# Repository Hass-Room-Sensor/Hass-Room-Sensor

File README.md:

# HASS Room Sensor

Home Assistant compatible sensor platform with ZigBee and ESPHome functionality.

## Hardware

* PCB: [`ecad/README.md`](ecad/README.md)
* Housing: [`mcad/README.md`](mcad/README.md)

## Firmware

For this please take a look at [`firmware/README.md`](firmware/README.md).

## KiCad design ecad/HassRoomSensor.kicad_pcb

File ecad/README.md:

# ecad

Room Sensor for Home Assistant.
There are two sensors that can be populated.

## BME690

* Temperature
* Humidity
* Pressure
* air quality (IAQ) level

## SCD4x

* Temperature
* Humidity
* CO2

The SCD4x has a higher accuracy with the pressure value of the BME690

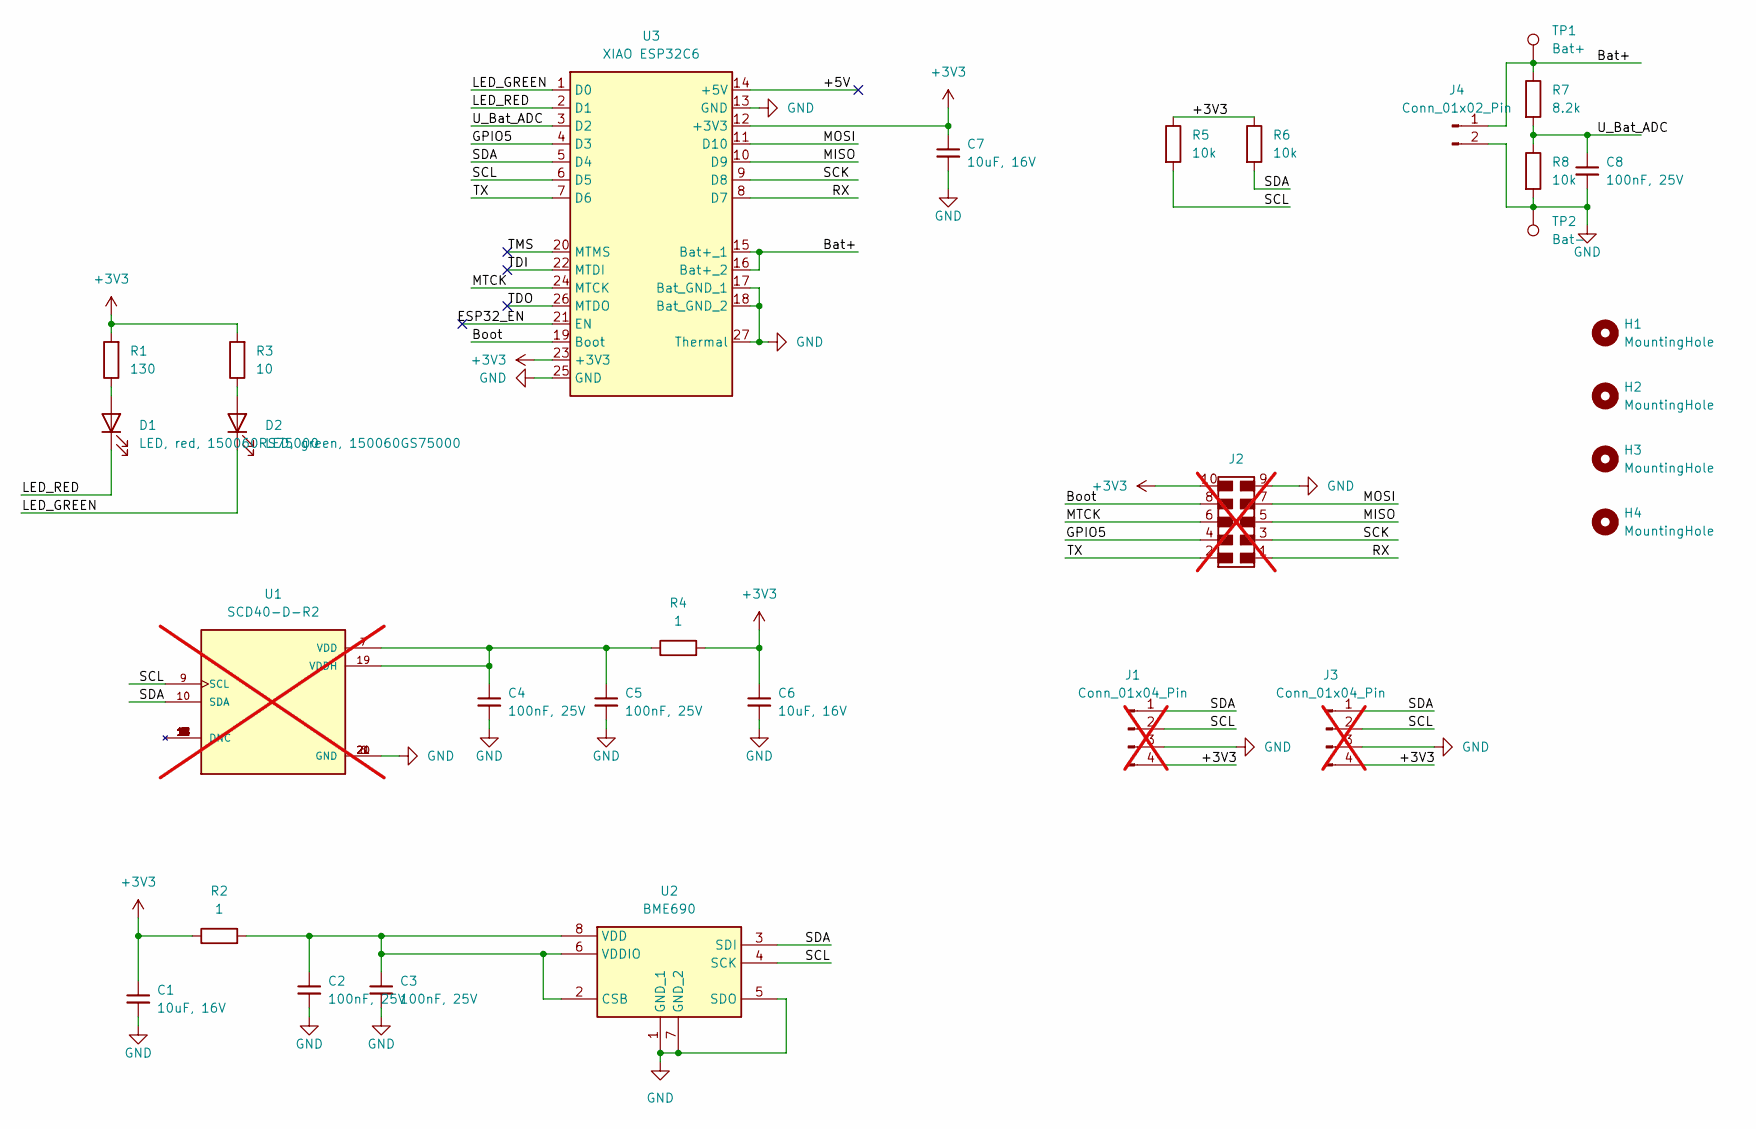
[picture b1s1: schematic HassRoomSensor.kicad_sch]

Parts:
C1, C6, C7: 10uF, 16V; C_0805_2012Metric; MPN CL21B106KOQNNNE; DigiKey 1276-2872-2-ND
C2, C3, C4, C5, C8: 100nF, 25V; C_0402_1005Metric; MPN CL05A104KA5NNNC; DigiKey 1276-1043-2-ND
D1: LED, red, 150060RS75000; D_0603_1608Metric; MPN 150060RS75000; DigiKey 732-4978-2-ND
D2: LED, green, 150060GS75000; D_0603_1608Metric; MPN 150060GS75000; DigiKey 732-4971-2-ND
H1, H2, H3, H4: MountingHole; MountingHole_2.1mm
J1, J3: Conn_01x04_Pin; PinHeader_1x04_P1.27mm_Vertical; not fitted
J2: 62131021021; J_Wurth_WR-PHD_62131021021; MPN 62131021021; DigiKey 732-62131021021TR-ND; not fitted
J4: Conn_01x02_Pin; JST_PH_S2B-PH-SM4-TB_1x02-1MP_P2.00mm_Horizontal; MPN S2B-PH-SM4-TB; DigiKey 455-S2B-PH-SM4-TBTR-ND
R1: 130; R_0603_1608Metric; MPN SR0603FR-7T130RL; DigiKey 13-SR0603FR-7T130RL-ND
R2: 1; R_0402_1005Metric; MPN RC0402FR-071RP; DigiKey 13-RC0402FR-071RPTR-ND
R3: 10; R_0603_1608Metric; MPN SR0603FR-0710RL; DigiKey 13-SR0603FR-0710RL-ND
R4: 1; R_0805_2012Metric; MPN SR0805FR-471RL; DigiKey YAG5851TR-ND
R5, R6, R8: 10k; R_0402_1005Metric; MPN RC0402FR-0710KP; DigiKey YAG1249TR-ND
R7: 8.2k; R_0402_1005Metric; MPN RC0402FR-138K2L; DigiKey 13-RC0402FR-138K2LTR-ND
TP1: Bat+; TestPoint_Keystone_5015_Micro_Mini
TP2: Bat-; TestPoint_Keystone_5015_Micro_Mini
U1: SCD40-D-R2; XDCR_SCD40-D-R2; PARTREV 1.2; not fitted
U2: BME690; MPN BME690; JLCPCB Part # BME690
U3: XIAO ESP32C6; XIAO-ESP32C6

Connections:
+3V3: C1.1, C6.1, C7.1, J1.4, J2.10, J3.4, R1.2, R2.1, R3.2, R4.2, R5.1, R6.1, U3.12 (+3V3), U3.23 (+3V3)
/+5V: U3.14 (+5V)
/Bat+: J4.1, R7.1, TP1.1, U3.15 (Bat+_1), U3.16 (Bat+_2)
/Boot: J2.8, U3.19 (Boot)
/ESP32_EN: U3.21 (EN)
/GPIO5: J2.4, U3.4 (D3)
/LED_GREEN: D2.1 (K), U3.1 (D0)
/LED_RED: D1.1 (K), U3.2 (D1)
/MISO: J2.5, U3.10 (D9)
/MOSI: J2.7, U3.11 (D10)
/MTCK: J2.6, U3.24 (MTCK)
/RX: J2.1, U3.8 (D7)
/SCK: J2.3, U3.9 (D8)
/SCL: J1.2, J3.2, R5.2, U1.9 (SCL), U2.4 (SCK), U3.6 (D5)
/SDA: J1.1, J3.1, R6.2, U1.10 (SDA), U2.3 (SDI), U3.5 (D4)
/TDI: U3.22 (MTDI)
/TDO: U3.26 (MTDO)
/TMS: U3.20 (MTMS)
/TX: J2.2, U3.7 (D6)
/U_Bat_ADC: C8.1, R7.2, R8.1, U3.3 (D2)
GND: C1.2, C2.2, C3.2, C4.2, C5.2, C6.2, C7.2, C8.2, J1.3, J2.9, J3.3, J4.2, R8.2, TP2.1, U1.6 (GND), U1.20 (GND), U1.21 (GND), U2.1 (GND_1), U2.5 (SDO), U2.7 (GND_2), U3.13 (GND), U3.17 (Bat_GND_1), U3.18 (Bat_GND_2), U3.25 (GND), U3.27 (Thermal)
unnamed: D1.2 (A), R1.1
unnamed: D2.2 (A), R3.1
unnamed: C4.1, C5.1, R4.1, U1.7 (VDD), U1.19 (VDDH)
unnamed: C2.1, C3.1, R2.2, U2.2 (CSB), U2.6 (VDDIO), U2.8 (VDD)

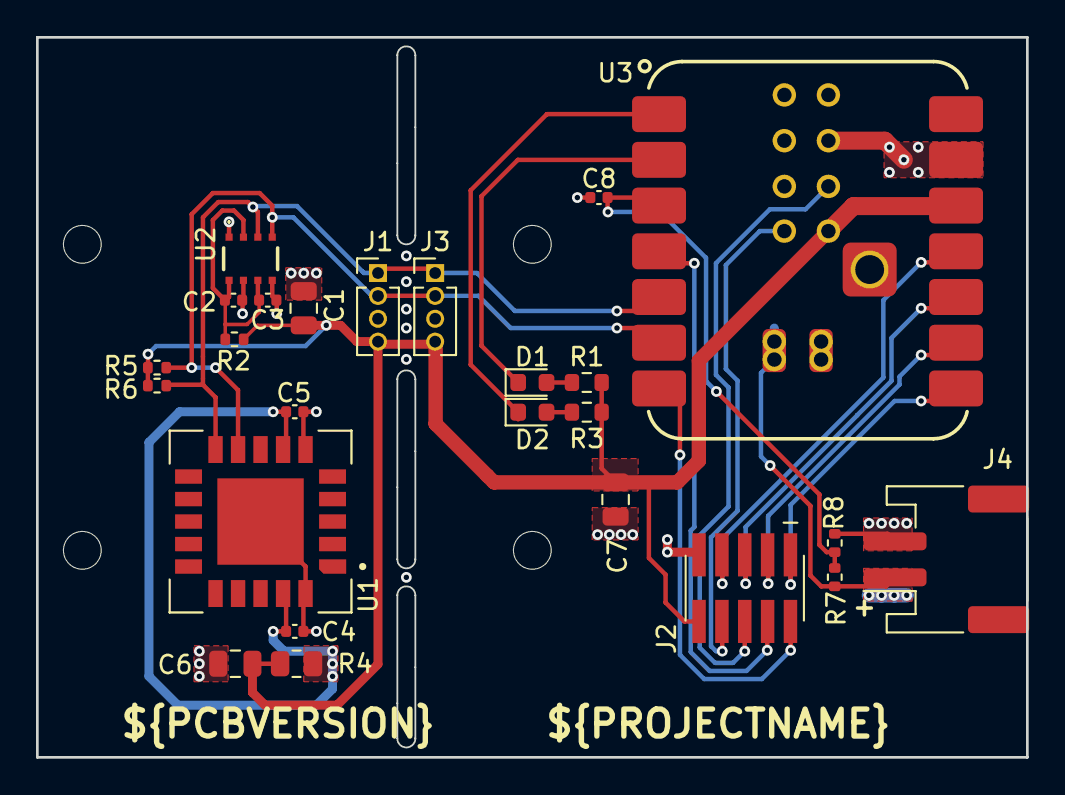
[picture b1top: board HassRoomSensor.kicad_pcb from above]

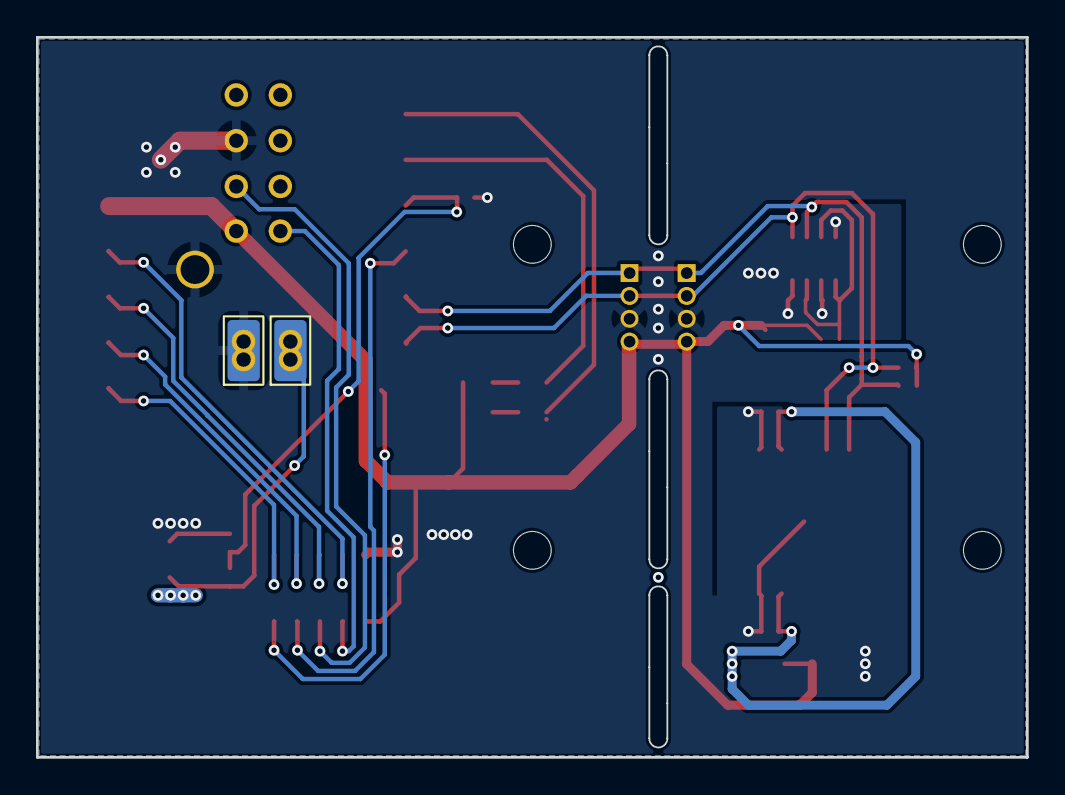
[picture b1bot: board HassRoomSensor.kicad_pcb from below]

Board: 2 copper layers, 55.0 x 40.0 mm, 31 parts (2 on the bottom side), 20 nets.

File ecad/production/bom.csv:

Designator,Footprint,Quantity,Value,LCSC Part #
"C1, C6, C7",0805,3,"10uF, 16V",CL21B106KOQNNNE
"C2, C3, C4, C5, C8",0402,5,"100nF, 25V",CL05A104KA5NNNC
D1,0603,1,"LED, red, 150060RS75000",150060RS75000
D2,0603,1,"LED, green, 150060GS75000",150060GS75000
J4,JST_PH_S2B-PH-SM4-TB_1x02-1MP_P2.00mm_Horizontal,1,Conn_01x02_Pin,S2B-PH-SM4-TB(LF)(SN)
R1,0603,1,130,RC0603FR-07130RL
R2,0402,1,1,RC0402FR-071RL
R3,0603,1,10,RC0603FR-0710RL
R4,0805,1,1,SR0805FR-471RL
"R5, R6, R8",0402,3,10k,RC0402FR-0710KL
R7,0402,1,8.2k,RC0402FR-078K2L
U2,BME690,1,BME690,BME690
U3,XIAO-ESP32C6,1,XIAO ESP32C6,

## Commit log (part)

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2023-04-23 Added suggestions for a hardware and software platform
2023-05-21 Moved hardware details to correct branch
2023-05-26 Initial ESP32 H2 framework
2023-05-26 CMake code cleanup
2023-05-26 Ignoring the clangd cache
2023-05-26 Added build instructions
2023-05-26 Basic LED and SCD41 framework
2023-05-27 RGB led support
2023-05-27 SCD41 framework
2023-05-28 Word based SCD41 implementation
2023-05-28 Fixed reading from SCD41
2023-05-28 Renamed functions to what they are called in the datasheet
2023-05-28 Not getting the serial number during SCD41 init
2023-05-28 Using the RGB to indicate the status
2023-05-28 Removed dead code
2023-05-28 Reduced the sleep time between check and get
2023-05-28 Printing measurements
2023-05-29 Code cleanup
2023-05-29 Added clang-{format, tidy} config
2023-05-29 ZigBee basic temp and hum sensor device
2023-06-04 Device name support
2023-07-01 Fixed setting ZigBee device model, manufacturer and version
2023-07-01 ZigBee power source configuration
2023-07-01 Framework for updating temperature values continuously
2023-08-11 SCD41 properly setting the altitude and obtaining config
2023-08-11 Updated to the latest zigbee component libs
2023-08-12 Humidity and value update support
2023-08-12 Added max humidity values
2023-08-12 Updated status
2023-09-24 Updated components
2023-09-24 Fixed rejoining a zigbee network
2023-09-30 Better RBG-Led state for the Zigbee device
2023-10-15 Updated dependencies
2023-10-15 CO2 cluster support
2023-10-15 Fixed ppm value representation
2023-10-21 Updated clangd compile commands path
2023-10-21 ZigBee factory reset input GPIO
2023-10-21 ZigBee power source type GPIO
2023-10-21 Fixed CO2 config and conversion
2023-10-22 Theoretical OTA support
2024-06-09 Removed debug code
2024-06-09 Updated to ESP-IDF 5.1.1
2024-06-09 Updated set target task to 5.1
2024-06-09 Removed the unused port for building the project
2024-06-09 Fixed using esp partition table
2024-06-09 Changed the OTA ZigBee file version back to 1
2024-06-09 Build and JTAG documentation
2024-06-09 ESP H2 Zigbee config
2024-06-09 ESP ZigBee light sleep
2024-06-09 Updated to esp-idf 5.1
2024-06-09 Zigbee code cleanup
2024-08-02 Simplified the measurement reading logic
2024-08-02 Updated to the latest ZigBee dependencies
2024-08-02 Added an erase-flash task
2024-08-02 Light sleep working without IO
2024-08-02 ZigBee commissioning working again
2024-08-02 SCD41 init test
2024-08-02 Sleep ready signal log info
2024-08-28 Migrated to the new i2c_master.h driver
2024-08-30 Better sensor write and read handling
2024-09-01 Fixed ZigBee device multiple init calls
2024-09-01 Fixed SCD41 read/write timeouts
2025-01-16 Zigbee device include cleanup
2025-01-16 SCD41 fixed probe result
2025-01-16 VSCode C++ language server config
2025-01-16 Enabled the LED again
2025-01-16 First step for the latest zigbee OTA
2025-01-17 Increased reporting intervals
2025-01-24 Zigbee device state decides over if device can sleep
2025-02-23 Mock SCD41
2025-02-23 Updated dependency lock
2025-02-23 Clang-Tidy
2025-02-23 Added full clean task
2025-02-23 Updated zigbee libs to 1.6.4
2025-03-02 Implemented missing OTA upgrade components
2025-03-02 Handling OTA abort messages
2025-03-02 OTA build CI
2025-03-02 Installing pushd
2025-03-02 Not using pushd in CI
2025-03-02 Run the espressif entry point manually
2025-03-02 Using full idf.py path
2025-03-02 Using the espressif action for building
2025-03-02 Removed lock file
2025-03-02 Fixed CI image_builder_tool.py
2025-03-02 Debug print
2025-03-02 CI cleanup
2025-03-02 Fixed ota json generator
2025-03-02 Converting to proper firmware file
2025-03-02 Disable ZigBee sleep during OTA
2025-03-02 Added OTA docs
2025-03-02 Added esp32_h2/dependencies.lock to .gitignore
2025-03-02 Updated feature list
2025-10-23 Updated to ESP IDF v5.5.1
2025-10-23 Try recover SCD41 sensors where the self tet failed
2025-10-23 Joining Zigbee networks is now faster and more reliable
2025-10-23 More reliable OTA
2025-10-23 Increased version to 1.1.0
2025-10-23 Corrected tile version
2025-10-23 Debug output fixes
2025-10-23 Debug and release sdkconfig
2025-10-23 Custom kconfig settings
2025-10-23 .gitignore add sdkconfig and sdkconfig.old
2025-10-23 esp32_h2 -> esp32
2025-10-23 Build for esp32_c6 and esp32_h2 inside the CI
2025-10-23 OTA merge CI
2025-10-23 CI strategy fixes
2025-10-23 Removed unnecessary files from merged output
2025-10-23 Fixed missing index.json CI artefact
2025-10-23 Debug output
2025-10-23 Disabled merge-multiple
2025-10-23 Removed CI debug output
2025-10-23 Parse OTA metadata in CI
2025-10-23 Typo
2025-10-24 Battery and LED control
2025-10-29 Debug RGB LED and SCD41 mock are configurable via menuconfig
2025-10-29 seed studio ESPC6 LED identify support
2025-10-30 Increased the self test timeout from 10 to 15s
2025-10-30 RGB LED handling the case where the NVS namespace does not yet exist
2025-10-30 Device definitions file
2025-11-02 Updated the README.md to reflect the latest changes
2025-11-02 Change the default flash size from 2MB to 4MB
2025-11-02 First version of a manual release job
2025-11-02 Better branch names
2025-11-02 Update the index.json and commit
2025-11-02 Added missing "
2025-11-02 Fix replace base URL
2025-11-02 Fixed JW quoting issue
2025-11-02 Added latest release artifacts to 'esp32/ota/index.json'
2025-11-02 Skip the CI for automatic commits
2025-11-02 Do not checkout in detached head state
2025-11-02 [skip ci] Added latest release artifacts to 'esp32/ota/index.json'
2025-11-02 Mark branch releases as pre-releases
2025-11-02 Run the release job only when manually started
2025-11-02 Add a Release CI (#1)
    Adds a manual workflow for publishing a new release and updating `esp32/ota/index.json`.
2025-11-02 added mcad dir
2025-11-02 added ecad dir
2025-11-02 added firmware/esphome
2025-11-02 moved esp32 firmware
2025-11-02 New sdkconfig based device selection
2025-11-02 Load the correct OTA image type inside the ZigBee device
2025-11-02 Fixed CI file syntax
2025-11-02 Also run automated CI if the target is develop
2025-11-02 Fixed CI device target name
2025-11-02 Fixed sdkconfig compilation issue
2025-11-02 New VSCode Task layout
2025-11-02 Fixed DeviceDefs.hpp path
2025-11-02 Fixed missing idf.py in set target tasks
2025-11-02 Fixed DeviceDefs.hpp path again
2025-11-02 Fixed the DeviceDefs.hpp path again²
2025-11-02 Removed pipefail
2025-11-02 Fixed device_target
2025-11-02 New sdkconfig based device selection (#2)
    * Selecting a device to build for is now purely defined by the `sdkconfig`.
    * New OTA image type numbering scheme.
    * The CI now builds images for all three supported devices.
    * Updated the README.md documentation to reflect all those changes.
2025-11-02 First battery measurement prototype
2025-11-02 updated/fixed JLCPCB part numbers
2025-11-10 Battery voltage reporting
2025-11-13 Corrected the battery ADC to mV conversion
2025-11-13 More battery percentage calculation fixes
2025-11-14 Report the battery as internal
2025-11-14 Reporting more battery details
2025-11-16 Reading the average battery level based on multiple measurements
2025-11-16 Removed an old comment
2025-11-16 Read Battery Level via ADC (#3)
2025-11-16 Added PCB design
2025-11-16 Fixed CI paths
2025-11-16 Fixed device defs path
2025-11-16 Added PCB design (#5)
2025-11-16 [skip ci] Added latest release artifacts to 'firmware/esp32/ota/index.json'
2025-11-16 Increased version to 1.3.0
2025-11-22 LED max brightness settings
2025-11-22 Device specific ZigBee event handling
2025-11-22 Increased version to 1.4.0
2025-11-22 Added documentation about the LED behavior
2025-11-22 Use the internal antenna by default
2025-11-23 Device Specific ZigBee Event Handler (#7)
2025-11-23 Ensure the ZigBee device is battery powered by default
2025-11-29 Reduced log level to debug
2025-11-29 Fixed red led not correctly indicating when device is in setup mode
2025-11-29 SDK config enabled sleep
2025-12-07 Mark battery percentage as reportable
2026-04-11 Refactor ESP32 firmware power reporting and fetch BME690 SensorAPI via CMake
    - add RTC-retained reporting state for deep-sleep wake cycles
    - report battery only on startup, percentage change, and daily keepalive
    - publish environmental values only when quantized readings change
    - add ZHA battery node-descriptor workaround for battery-powered end devices
    - replace vendored BME690 SensorAPI copy with CMake FetchContent
    - update firmware docs for ZHA compatibility and build behavior
2026-04-11 More debug logs
2026-04-12 Fixed ZigBee connection
2026-04-12 Light sleep support so the device stays connected via Zigbee
2026-04-14 Fixed light sleep and initial setup
2026-04-18 Fixed identify crash
2026-04-18 Fixed crashes around sensor readings when not initialized
2026-04-18 Fixed red LED GPIO conflict
2026-04-18 Added KiCad temporary files to .gitignore
2026-04-18 Make LED classes not copyable to prevent undefined state
2026-04-18 Fixed device not entering light sleep again
2026-04-18 Updated ESP IDF to 6.0 for CI
